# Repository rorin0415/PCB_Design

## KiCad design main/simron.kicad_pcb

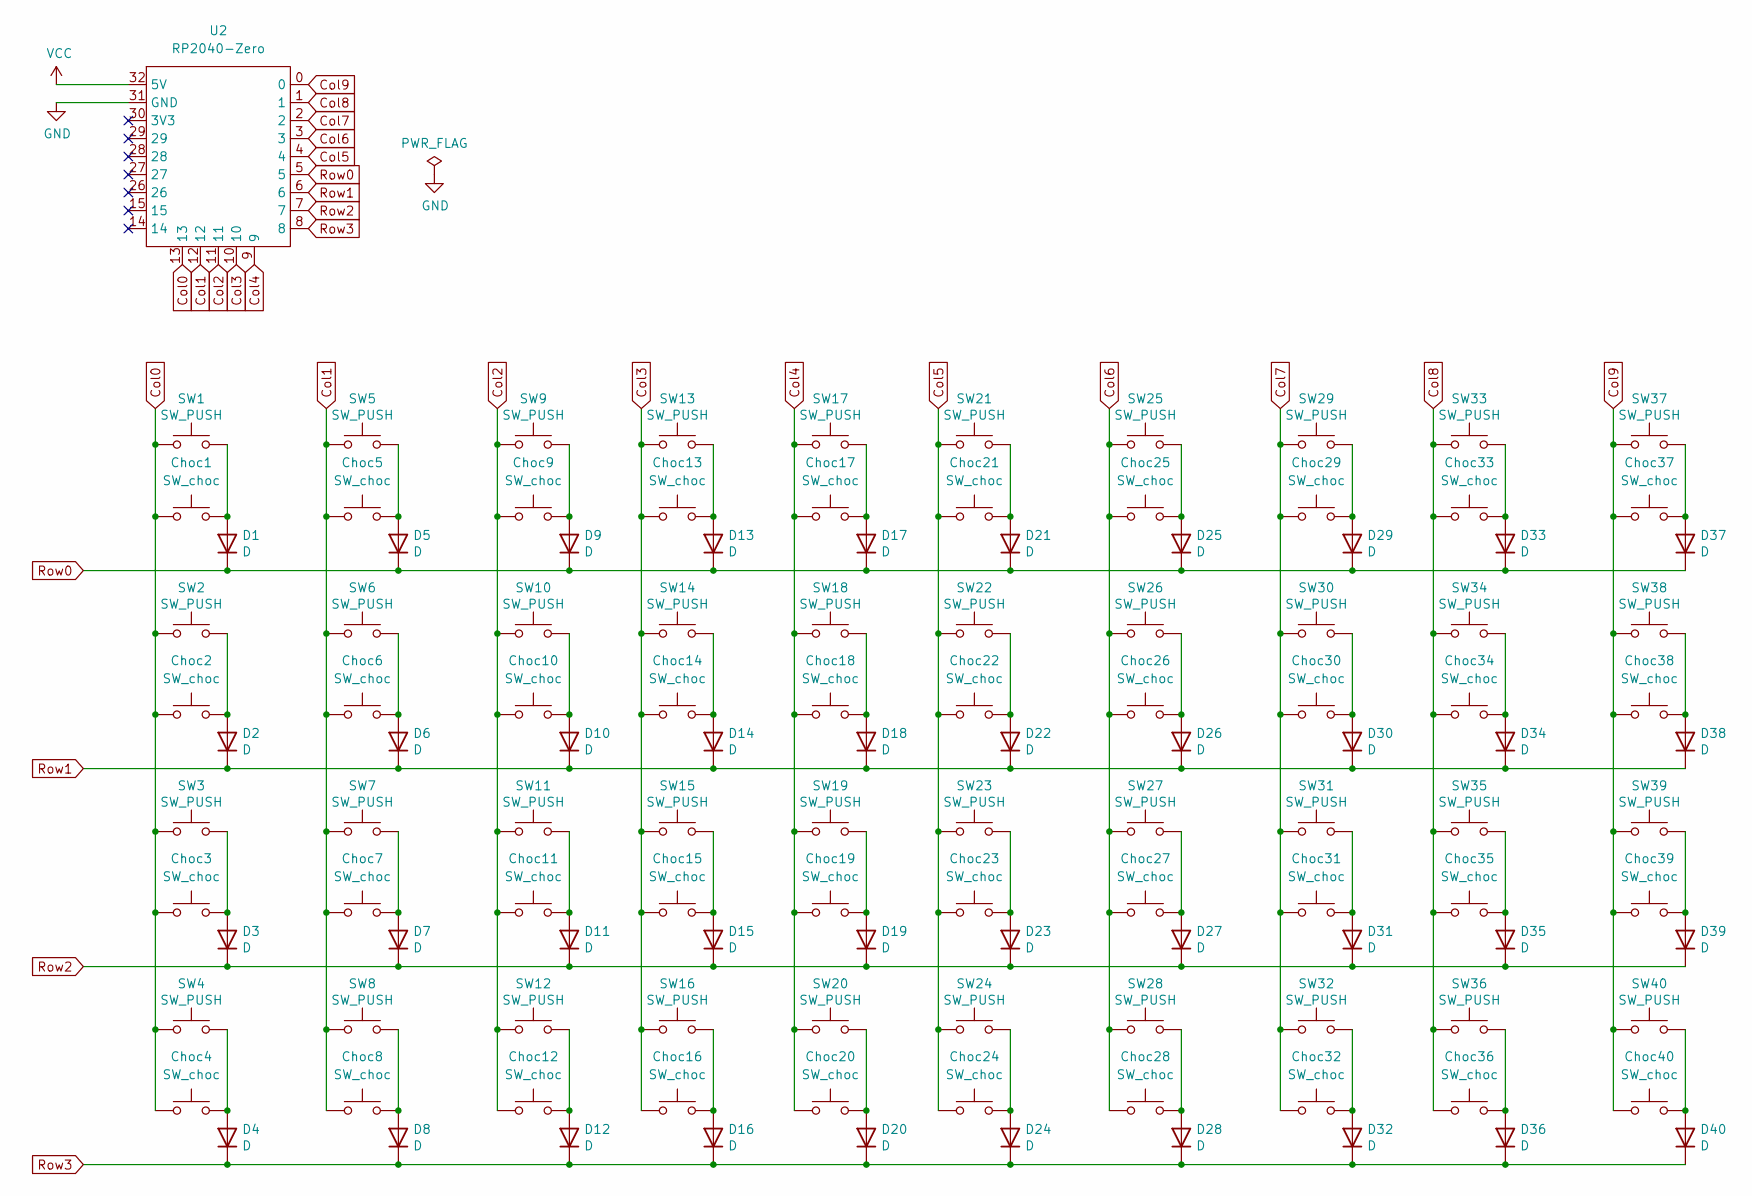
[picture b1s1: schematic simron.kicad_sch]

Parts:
Choc1, Choc2, Choc3, Choc4, Choc5, Choc6, Choc7, Choc8, Choc9, Choc10, Choc11, Choc12, Choc13, Choc14, Choc15, Choc16, Choc17, Choc18, Choc19, Choc20, Choc21, Choc22, Choc23, Choc24, Choc25, Choc26, Choc27, Choc28, Choc29, Choc30, Choc31, Choc32, Choc33, Choc34, Choc35, Choc36, Choc37, Choc38, Choc39, Choc40: SW_choc; Choc_Hotswap_1u
D1, D2, D3, D4, D5, D6, D7, D8, D9, D10, D11, D12, D13, D14, D15, D16, D17, D18, D19, D20, D21, D22, D23, D24, D25, D26, D27, D28, D29, D30, D31, D32, D33, D34, D35, D36, D37, D38, D39, D40: D; Diode_SMD
SW1, SW2, SW3, SW4, SW5, SW6, SW7, SW8, SW9, SW10, SW11, SW12, SW13, SW14, SW15, SW16, SW17, SW18, SW19, SW20, SW21, SW22, SW23, SW24, SW25, SW26, SW27, SW28, SW29, SW30, SW31, SW32, SW33, SW34, SW35, SW36, SW37, SW38, SW39, SW40: SW_PUSH; CherryMX_Hotswap_1u
U2: RP2040-Zero

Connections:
Col0: Choc1.1, Choc2.1, Choc3.1, Choc4.1, SW1.1, SW2.1, SW3.1, SW4.1, U2.13
Col1: Choc5.1, Choc6.1, Choc7.1, Choc8.1, SW5.1, SW6.1, SW7.1, SW8.1, U2.12
Col2: Choc9.1, Choc10.1, Choc11.1, Choc12.1, SW9.1, SW10.1, SW11.1, SW12.1, U2.11
Col3: Choc13.1, Choc14.1, Choc15.1, Choc16.1, SW13.1, SW14.1, SW15.1, SW16.1, U2.10
Col4: Choc17.1, Choc18.1, Choc19.1, Choc20.1, SW17.1, SW18.1, SW19.1, SW20.1, U2.9
Col5: Choc21.1, Choc22.1, Choc23.1, Choc24.1, SW21.1, SW22.1, SW23.1, SW24.1, U2.4
Col6: Choc25.1, Choc26.1, Choc27.1, Choc28.1, SW25.1, SW26.1, SW27.1, SW28.1, U2.3
Col7: Choc29.1, Choc30.1, Choc31.1, Choc32.1, SW29.1, SW30.1, SW31.1, SW32.1, U2.2
Col8: Choc33.1, Choc34.1, Choc35.1, Choc36.1, SW33.1, SW34.1, SW35.1, SW36.1, U2.1
Col9: Choc37.1, Choc38.1, Choc39.1, Choc40.1, SW37.1, SW38.1, SW39.1, SW40.1, U2.0
GND: U2.31 (GND)
unnamed: Choc1.2, D1.2 (A), SW1.2
unnamed: Choc2.2, D2.2 (A), SW2.2
unnamed: Choc3.2, D3.2 (A), SW3.2
unnamed: Choc4.2, D4.2 (A), SW4.2
unnamed: Choc5.2, D5.2 (A), SW5.2
unnamed: Choc6.2, D6.2 (A), SW6.2
unnamed: Choc7.2, D7.2 (A), SW7.2
unnamed: Choc8.2, D8.2 (A), SW8.2
unnamed: Choc9.2, D9.2 (A), SW9.2
unnamed: Choc10.2, D10.2 (A), SW10.2
unnamed: Choc11.2, D11.2 (A), SW11.2
unnamed: Choc12.2, D12.2 (A), SW12.2
unnamed: Choc13.2, D13.2 (A), SW13.2
unnamed: Choc14.2, D14.2 (A), SW14.2
unnamed: Choc15.2, D15.2 (A), SW15.2
unnamed: Choc16.2, D16.2 (A), SW16.2
unnamed: Choc17.2, D17.2 (A), SW17.2
unnamed: Choc18.2, D18.2 (A), SW18.2
unnamed: Choc19.2, D19.2 (A), SW19.2
unnamed: Choc20.2, D20.2 (A), SW20.2
unnamed: Choc21.2, D21.2 (A), SW21.2
unnamed: Choc22.2, D22.2 (A), SW22.2
unnamed: Choc23.2, D23.2 (A), SW23.2
unnamed: Choc24.2, D24.2 (A), SW24.2
unnamed: Choc25.2, D25.2 (A), SW25.2
unnamed: Choc26.2, D26.2 (A), SW26.2
unnamed: Choc27.2, D27.2 (A), SW27.2
unnamed: Choc28.2, D28.2 (A), SW28.2
unnamed: Choc29.2, D29.2 (A), SW29.2
unnamed: Choc30.2, D30.2 (A), SW30.2
unnamed: Choc31.2, D31.2 (A), SW31.2
unnamed: Choc32.2, D32.2 (A), SW32.2
unnamed: Choc33.2, D33.2 (A), SW33.2
unnamed: Choc34.2, D34.2 (A), SW34.2
unnamed: Choc35.2, D35.2 (A), SW35.2
unnamed: Choc36.2, D36.2 (A), SW36.2
unnamed: Choc37.2, D37.2 (A), SW37.2
unnamed: Choc38.2, D38.2 (A), SW38.2
unnamed: Choc39.2, D39.2 (A), SW39.2
unnamed: Choc40.2, D40.2 (A), SW40.2
Row0: D1.1 (K), D5.1 (K), D9.1 (K), D13.1 (K), D17.1 (K), D21.1 (K), D25.1 (K), D29.1 (K), D33.1 (K), D37.1 (K), U2.5
Row1: D2.1 (K), D6.1 (K), D10.1 (K), D14.1 (K), D18.1 (K), D22.1 (K), D26.1 (K), D30.1 (K), D34.1 (K), D38.1 (K), U2.6
Row2: D3.1 (K), D7.1 (K), D11.1 (K), D15.1 (K), D19.1 (K), D23.1 (K), D27.1 (K), D31.1 (K), D35.1 (K), D39.1 (K), U2.7
Row3: D4.1 (K), D8.1 (K), D12.1 (K), D16.1 (K), D20.1 (K), D24.1 (K), D28.1 (K), D32.1 (K), D36.1 (K), D40.1 (K), U2.8
VCC: U2.32 (5V)

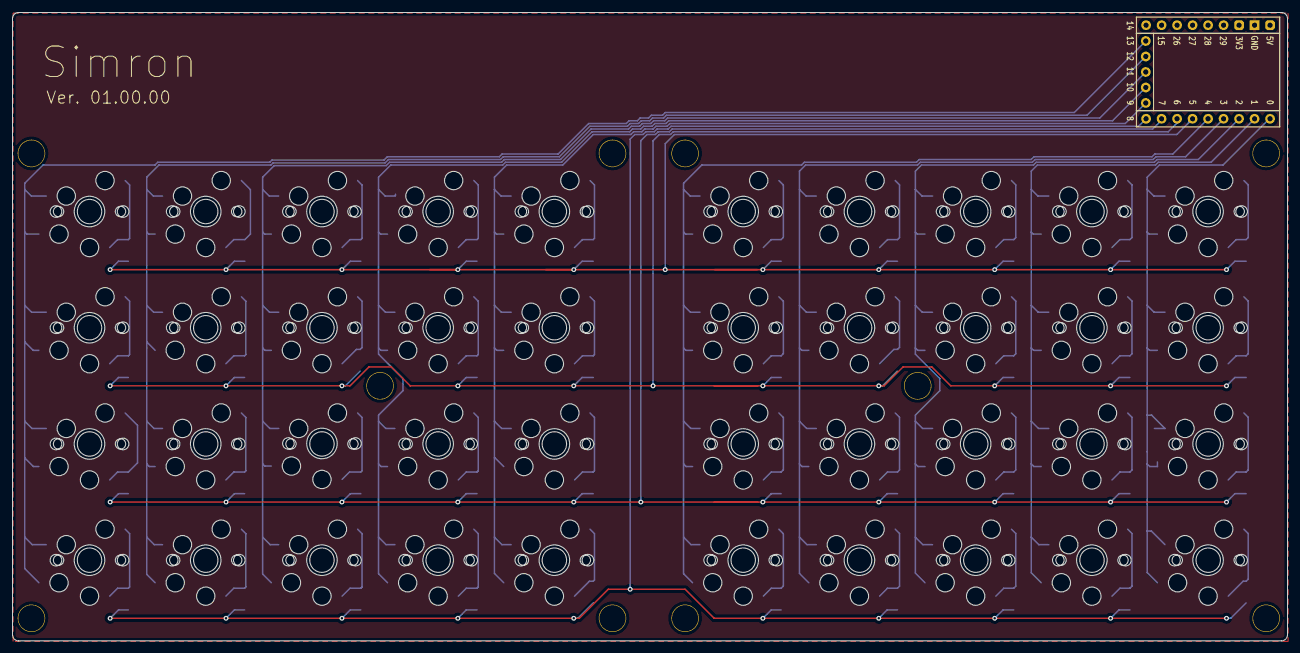
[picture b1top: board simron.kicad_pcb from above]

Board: 2 copper layers, 209.0 x 103.0 mm, 131 parts (0 on the bottom side), 54 nets.

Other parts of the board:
Ref**: Val**; m2_Spacer_Hole
Ref**#2, Ref**#3, Ref**#4, Ref**#5, Ref**#6, Ref**#7, Ref**#8, Ref**#9, Ref**#10: Val**; m2_Spacer_Hole

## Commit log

2025-12-02 基板設計をコミット
2026-04-17 ライブラリをいったん登録
2026-04-17 XIAOの環境をコミット
2026-04-17 不要なので削除
